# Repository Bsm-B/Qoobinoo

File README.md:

# Qoobinno

is a fully integrated platform designed to teach beginners or children
the concepts of programming and embdded AI/ML. 

It consists of both hardware and software components, including an Atmel 32u4 microcontroller development board and a fully integrated graphical programming for any type of Arduino projects, ready to install in your computer, it works offline and also online

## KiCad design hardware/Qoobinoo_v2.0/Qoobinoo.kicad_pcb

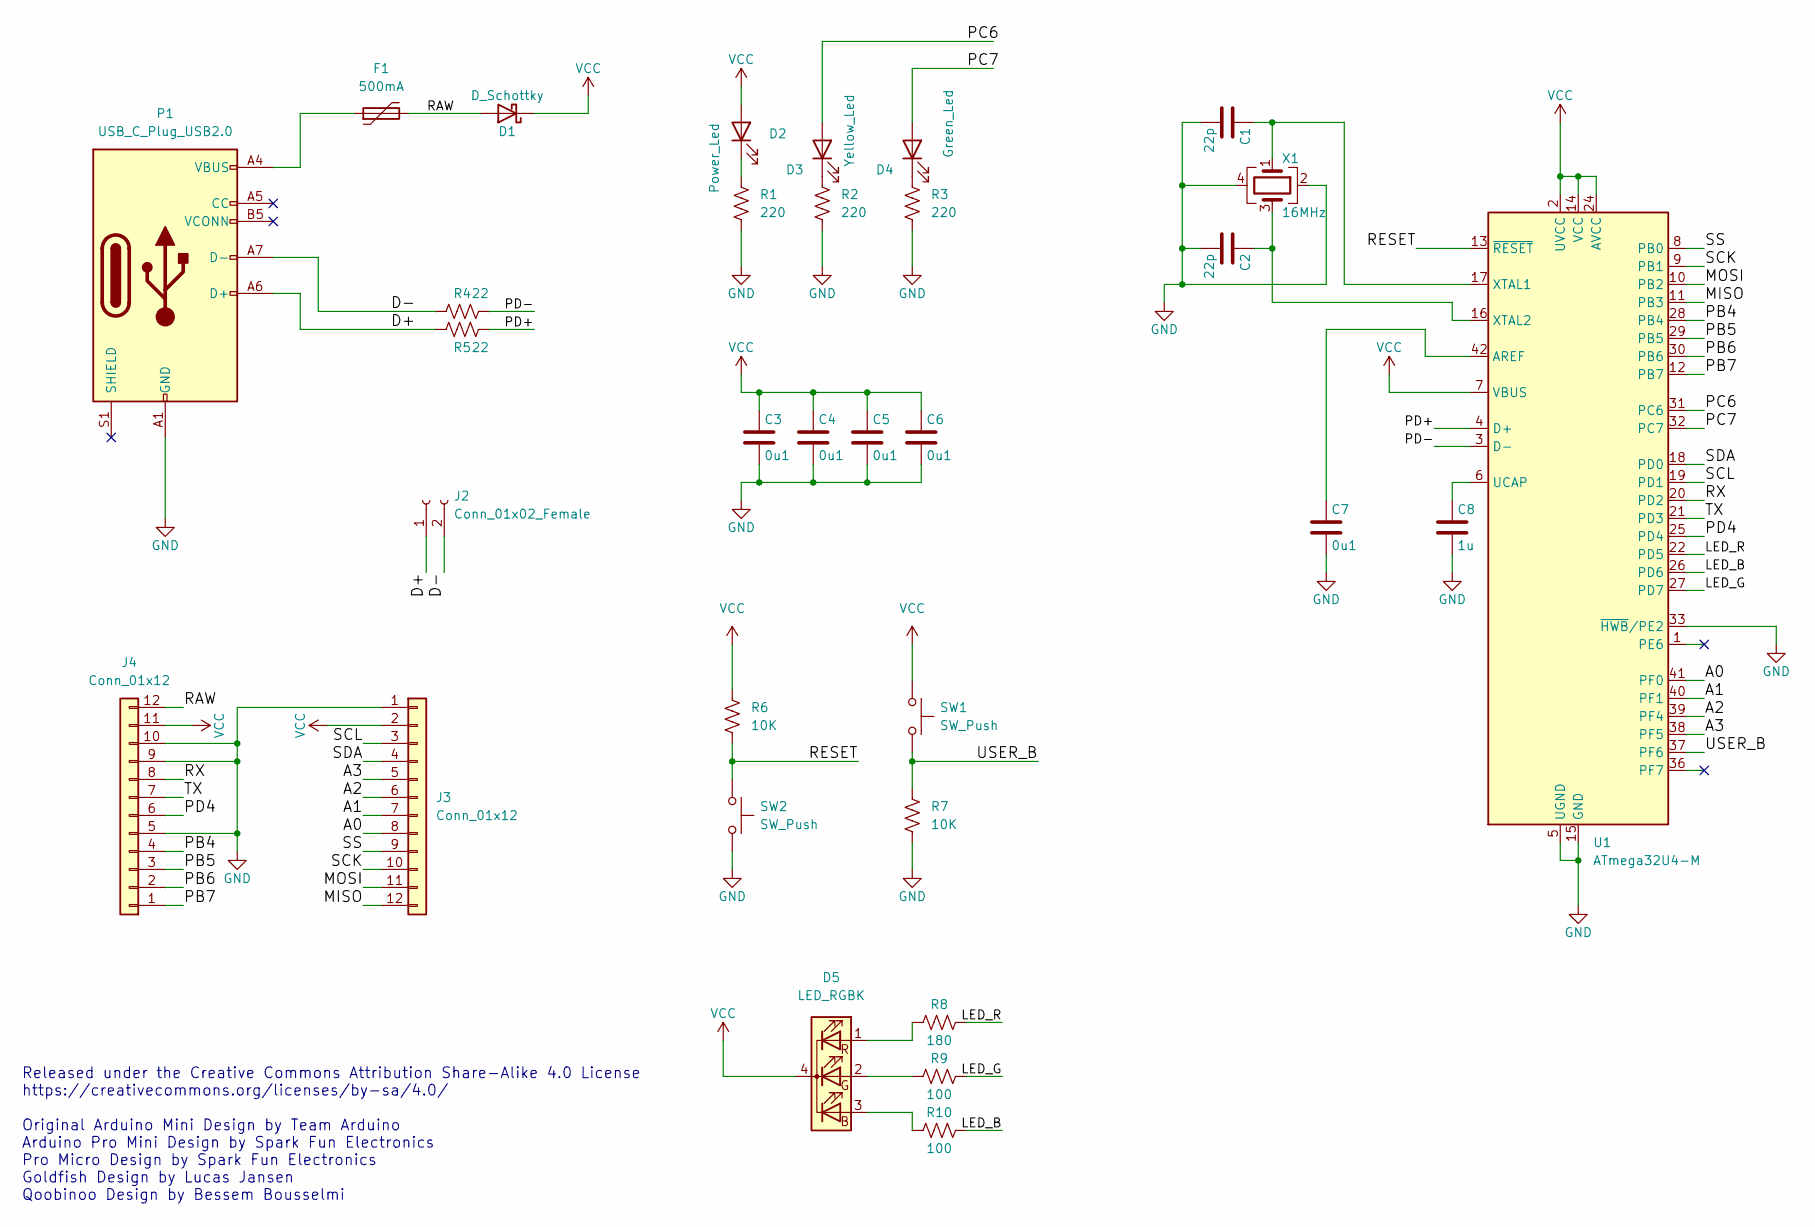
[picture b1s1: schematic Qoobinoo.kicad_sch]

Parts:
C1, C2: 22p; C_0805_2012Metric
C3, C4, C5, C6, C7: 0u1; C_1206_3216Metric
C8: 1u; C_1206_3216Metric
D1: D_Schottky; D_PowerDI-123
D2: Power_Led; LED_1206_3216Metric
D3: Yellow_Led; LED_1206_3216Metric
D4: Green_Led; LED_1206_3216Metric
D5: LED_RGBK; LED_Avago_PLCC4_3.2x2.8mm_CW
F1: 500mA; Fuse_0805_2012Metric
J2: Conn_01x02_Female; Pins_1x02
J3, J4: Conn_01x12; Pins_x12
P1: USB_C_Plug_USB2.0; USB_C_Receptacle_CNCTech_C-ARA1-AK51X
R1, R2, R3: 220; R_1206_3216Metric
R4, R5: 22; R_0805_2012Metric
R6, R7: 10K; R_1206_3216Metric
R8: 180; R_1206_3216Metric
R9, R10: 100; R_1206_3216Metric
SW1, SW2: SW_Push; SW_Push_SPST_NO_Alps_SKRK
U1: ATmega32U4-M; TQFP-44-1EP_10x10mm_P0.8mm_EP4.5x4.5mm
X1: 16MHz; Crystal_SMD_SeikoEpson_FA238-4Pin_3.2x2.5mm

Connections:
/A0: J3.8, U1.41 (PF0)
/A1: J3.7, U1.40 (PF1)
/A2: J3.6, U1.39 (PF4)
/A3: J3.5, U1.38 (PF5)
/D+: J2.1, P1.A6 (D+), R5.1
/D-: J2.2, P1.A7 (D-), R4.1
/LED_B: R10.2, U1.26 (PD6)
/LED_G: R9.2, U1.27 (PD7)
/LED_R: R8.2, U1.22 (PD5)
/MISO: J3.12, U1.11 (PB3)
/MOSI: J3.11, U1.10 (PB2)
/PB4: J4.4, U1.28 (PB4)
/PB5: J4.3, U1.29 (PB5)
/PB6: J4.2, U1.30 (PB6)
/PB7: J4.1, U1.12 (PB7)
/PC6: D3.2 (A), U1.31 (PC6)
/PC7: D4.2 (A), U1.32 (PC7)
/PD4: J4.6, U1.25 (PD4)
/PD+: R5.2, U1.4 (D+)
/PD-: R4.2, U1.3 (D-)
/RAW: D1.2 (A), F1.2, J4.12
/RESET: R6.2, SW2.1, U1.13 (~RESET)
/RX: J4.8, U1.20 (PD2)
/SCK: J3.10, U1.9 (PB1)
/SCL: J3.3, U1.19 (PD1)
/SDA: J3.4, U1.18 (PD0)
/SS: J3.9, U1.8 (PB0)
/TX: J4.7, U1.21 (PD3)
/USER_B: R7.1, SW1.2, U1.37 (PF6)
GND: C1.2, C2.2, C3.2, C4.2, C5.2, C6.2, C7.2, C8.2, J3.1, J4.5, J4.9, J4.10, P1.A1 (GND), P1.A12 (GND), P1.B1 (GND), P1.B12 (GND), R1.2, R2.2, R3.2, R7.2, SW2.2, U1.5 (UGND), U1.15 (GND), U1.23 (GND), U1.33 (~HWB/PE2), U1.35 (GND), U1.43 (GND), U1.45 (GND), X1.2, X1.4
unnamed: C1.1, U1.17 (XTAL1), X1.1
unnamed: C2.1, U1.16 (XTAL2), X1.3
unnamed: C7.1, U1.42 (AREF)
unnamed: C8.1, U1.6 (UCAP)
unnamed: D2.1 (K), R1.1
unnamed: D3.1 (K), R2.1
unnamed: D4.1 (K), R3.1
unnamed: D5.1 (RA), R8.1
unnamed: D5.2 (GA), R9.1
unnamed: D5.3 (BA), R10.1
unnamed: F1.1, P1.A4 (VBUS), P1.A9 (VBUS), P1.B4 (VBUS), P1.B9 (VBUS)
VCC: C3.1, C4.1, C5.1, C6.1, D1.1 (K), D2.2 (A), D5.4 (K), J3.2, J4.11, R6.1, SW1.1, U1.2 (UVCC), U1.7 (VBUS), U1.14 (VCC), U1.24 (AVCC), U1.34 (VCC), U1.44 (AVCC)

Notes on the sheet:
Released under the Creative Commons Attribution Share-Alike 4.0 License https://creativecommons.org/licenses/by-sa/4.0/ Original Arduino Mini Design by Team Arduino Arduino Pro Mini Design by Spark Fun Electronics Pro Micro Design by Spark Fun Electronics Goldfish Design by Lucas Jansen Qoobinoo De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

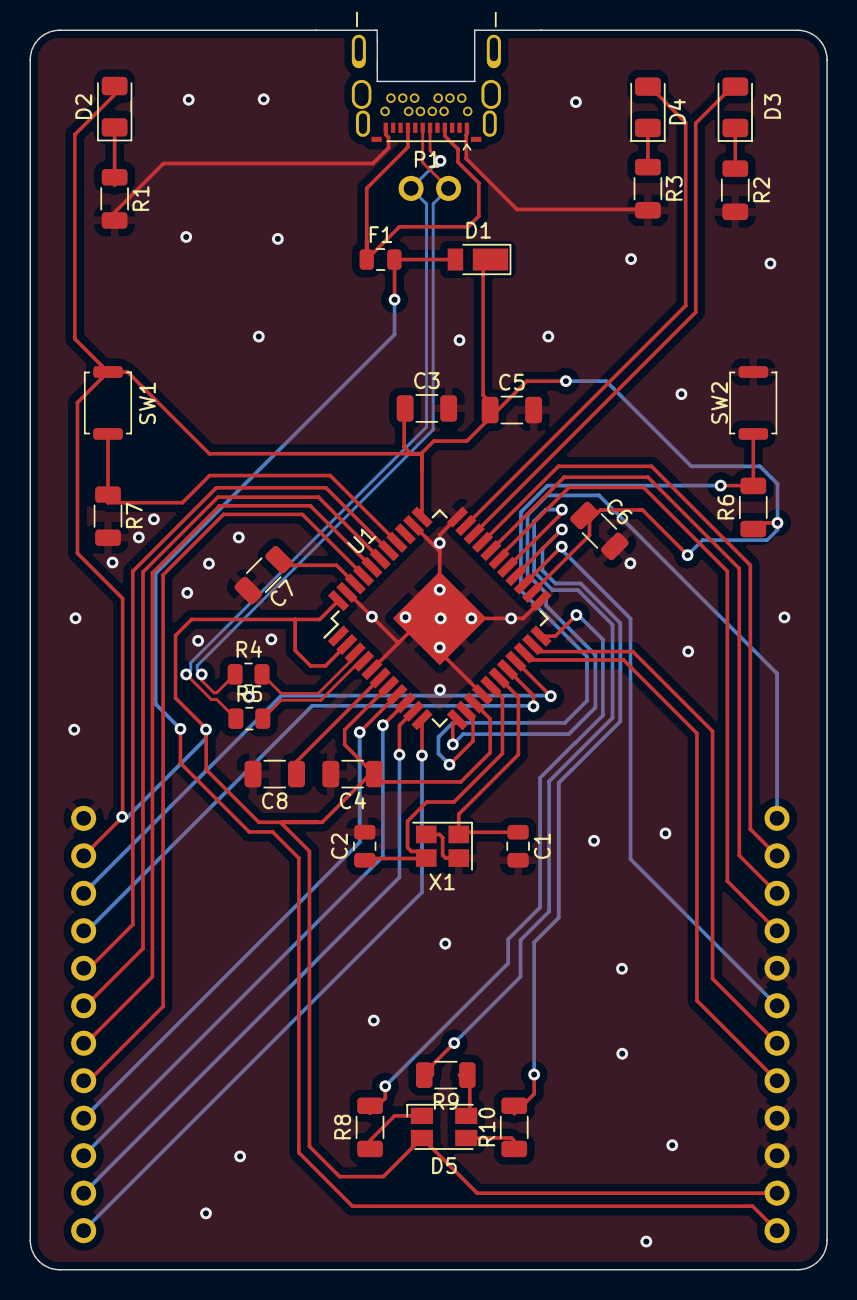
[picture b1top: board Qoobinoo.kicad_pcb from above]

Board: 2 copper layers, 54.0 x 84.0 mm, 32 parts (0 on the bottom side), 42 nets.

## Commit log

2023-03-17 add coming_soon website
2023-03-19 update index, add new style , add meta for social media
2023-03-26 dev board hardware design 📟
2023-08-07 Change USB
2023-08-07 generate gerber
